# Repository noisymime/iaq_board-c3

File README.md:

# IAQ C3 (Indoor Air Quality) Board 
IAQ Board is a DIY (Do-It-Yourself) device for measuring internal air quality. This device is a fork of the [amazing work by Nikolay Kitanov](https://github.com/nkitanov/iaq_board) with the goals of updating the PCB to use the newer ESP32-C3 and to provide a more complete case and stand solution. 

**And here is my device. I am publishing all the details and documentation under '[open source hardware](https://en.wikipedia.org/wiki/Open-source_hardware)' CC-BY-CA license, so everyone can build, adapt and sell it, as long as share under the same license**

**Table of Contents**
   * [IAQ (Indoor Air Quality) Board](#iaq-indoor-air-quality-board)
      * [What exactly is this thing?](#what-exactly-is-this-thing)
      * [Who can build it?](#who-can-build-it)
      * [What about ordering a device?](#what-about-ordering-a-device)
   * [Components Details](#components-details)
      * [1. PCB](#1-pcb)
      * [2. Holder case](#2-holder-case)
      * [3. Microcontroller Board](#3-microcontroller-board)
      * [4. Dust Sensor](#4-dust-sensor)
      * [5. CO2 sensor](#5-co2-sensor)
      * [6. Temperature/Humidity/Pressure sensor](#6-temperaturehumiditypressure-sensor)
      * [7. Ambient Light Sensor](#7-ambient-light-sensor)
      * [8. LEDs](#8-leds)
      * [9. Displays](#9-displays)
      * [10. Volatile Organic Compound sensor](#10-volatile-organic-compound-sensor)
      * [11. Other electrical components](#11-other-electrical-components)
      * [Can you skip components?](#can-you-skip-components)
   * [Bill of Materials (BOM)](#bill-of-materials-bom)
   * [Firmware](#firmware)
   * [Schematic](#schematic)
   * [Soldering tips](#soldering-tips)
   * [User manual](#user-manual)
         * [Multi function button](#multi-function-button)
         * [LED Brightness control and correction](#led-brightness-control-and-correction)
   * [FAQ](#faq)
            * [<em>Can I power it from a battery?</em>](#can-i-power-it-from-a-battery)
            * [<em>Can it be installed outdoors?</em>](#can-it-be-installed-outdoors)
            * [<em>How to calibrate MH-Z19B CO2 sensor?</em>](#how-to-calibrate-mh-z19b-co2-sensor)
            * [<em>How to calibrate SGP30 VOC sensor?</em>](#how-to-calibrate-sgp30-voc-sensor)
            * [<em>How to connect to WiFi?</em>](#how-to-connect-to-wifi)
            * [<em>How to add it in Home Assistant?</em>](#how-to-add-it-in-home-assistant)
            * [<em>What if some of the sensors/displays is disconnected while the device works?</em>](#what-if-some-of-the-sensorsdisplays-is-disconnected-while-the-device-works)
         * [<em>What about short circuits of the exposed electronics?</em>](#what-about-short-circuits-of-the-exposed-electronics)
   * [More Tech Details](#more-tech-details)
   * [Known issues](#known-issues)
   * [License](#license)

## What exactly is this thing?
The device is based on widely available and cheap essential components ([MCU](https://en.wikipedia.org/wiki/Microcontroller) and sensors). The core component is a simple [PCB](https://en.wikipedia.org/wiki/Printed_circuit_board) (printed circuit board) that's why I called it **IAQ Board**. The board integrates all the components in a very small footprint (size of a cigarette box). All parts are soldered on it and everyone can assemble it with basic soldering skills. The total price if you build it yourself is about $75 AUD. For these amount of money you get the following air parameters measured adequately (you might not install all sensors if you want to save money): 
- [X] ***Temperature / Humidity / Pressure***
- [X] [***Air particles PM1, PM2.5, PM10***](https://en.wikipedia.org/wiki/Particulates)
- [X] [***Carbon Dioxide with NDIR sensor***](https://en.wikipedia.org/wiki/Indoor_air_quality#Carbon_dioxide)
- [X] [***Air Quality Index by EPA, based on 24h average PM2.5 particles***](https://airindex.eea.europa.eu/Map/AQI/Viewer/)
- [X] [***Ambient light***](https://en.wikipedia.org/wiki/Illuminance)
- [X] [***Total VOC (volatile organic compound)***](https://en.wikipedia.org/wiki/Volatile_organic_compound)
- [X] ***equivalent CO2 (not very correct compared with the NDIR sensor, but it's provided by the VOC sensor)***

**On top of that:**
- [X] ***One OLED display to show the data ***
- [X] ***three RGB wide angle LEDs with auto brightness. LED1 indicates PM2.5, LED2 - Air quality index, LED3 - CO2.*** 
- [X] ***auto night dimming of the displays and LEDs (can be disabled)***
- [X] ***MIN/MAX values of Temperature, PM2.5 and CO2, and 24h average PM2.5 value.***
- [X] ***multi function button for selection of the data to show on the display***
- [X] ***[firmware](https://en.wikipedia.org/wiki/Firmware) based on [ESPhome](https://esphome.io/), the device can be [directly added](https://esphome.io/components/api.html) in [Home Assistant](https://www.home-assistant.io/)***
- [X] ***WiFi access to the device with http server and [REST API](https://esphome.io/web-api/index.html) and [esphome native API](https://esphome.io/components/api.html)  to read the sensor data***

## Who can build it?
The device is just a simple PCB board and almost everyone with some soldering skills can assemble it in a few steps:
1. [Download the PCB files](kicad/) and print the PCB somewhere like https://jlcpcb.com/
2. Buy some components (listed in the bill of materials section) from Aliexpress or any other source.
3. Solder everything on the board. With the exception of the ambient light sensor, all the rest is pretty easy with general soldering skills. Soldering light sensor can be done with regular soldering iron, but because of the small size of the IC, it's easier if you have heat gun or SMD reflow oven/plate. [Here is video how to complete device from assembled PCB.](https://www.youtube.com/watch?v=b2oDBgN3h1w)
4. Flash the microcontroller with the esphome firmware [following the manual](firmware/). You can write your own firmware if you have the skills. :smile: 
5. Print the holder case on 3D printer if you wish. I have some sensors without it and they are perfectly fine, so it's up to you.

If you have experience with electronics and microcontrollers just check the [schematics](kicad/) and make whatever you wish - build your own firmware, do another PCB, connect external sensors, don't use it at all because you can make it better :smile:. The device is quite simple for embedded electronics enthusiasts anyway...

## What about ordering a device?
I made this device for me and then decided to share it. I think a lot of people might be interested to have such air quality sensor. I did not have intension to make money from it, that's why it's "open hardware" and I publish all of the information, so everyone can build it. 

However I know that someone might be interested in the device, but lack the skills to build it. [Please follow this link for more details.](ordering.md)

# Components Details

## 1. PCB

The PCB (printed circuit board) is very simple and compact. It's 70x43mm (photos above are showing it larger than the actual size). It just connects a few sensors, microcontroller and displays. I wanted to integrate it in as much smaller footprint as possible, so the whole device is like a cigarette box. Most of the parts are surface mounted which makes the soldering just a bit more complicated, but still not a big deal. And of course it could be integrated even more by soldering all individual components on the PCB but then it's not really a hobby project anymore and much more difficult to build it.
It's designed on [KiCad](https://kicad.org/) and in the [kicad folder](kicad/) you can find full KiCad project, PCB gerber files, etc.
## 2. Holder case

STL files for a case and stand are provided and can be printed on any standrd 3D printer.

## 3. Microcontroller Board
This is the primary difference between this board and the original by [nkitanov](https://github.com/nkitanov/iaq_board). I am using the newer ESP32-C3 Supermini which is not only faster and more compact, but has a USB-C connector on it rather than micro-USB

## 4. Dust Sensor

Dust sensor is the Chinese [Plantower PMS7003]([http://www.plantower.com/en/content/?110.html](https://www.plantower.com/en/products_33/76.html)) - 1, 2.5 and 10 micron particle laser sensor. It's very small and is perfect for indoor environment. 
## 5. CO2 sensor

Carbon dioxide sensor is the Chinese [Winsen MH-Z19B](https://www.winsen-sensor.com/sensors/co2-sensor/mh-z19b.html) - the most expensive part of the device. It's quite popular for hobby air quality meters and can [adequatly measure](https://www.circuits.dk/testing-mh-z19-ndir-co2-sensor-module/) up to 5000 ppm CO2 concentration.

**Keep in mind that there are some fake MH-Z19B sensors, [explained here](https://revspace.nl/MH-Z19B#Fake_MH-Z19B_.28black_PCB.29).**
## 6. Temperature/Humidity/Pressure sensor

This sensor is the popular [Bosch BME280](https://www.bosch-sensortec.com/products/environmental-sensors/humidity-sensors-bme280/), mounted on 3.3V only breakout board from China. There are also smaller [breakout boards](http://www.cncroutersource.com/breakout-boards.html) from China working both on 5V and 3.3V, but these have voltage regulator which can theoretically warm the board and change the temperature reading. That's why I use the boards with 3.3V only.

**Please note that due to semiconductor shortage these are difficult to find now (June 2021). I am currently using my own breakout where I solder the BME directly. BME280 as IC can be found occasionally in stock from DigiKey**
## 7. Ambient Light Sensor

The light sensor is [TSL 2561](https://ams.com/tsl2561) and it's the only sensor you need to solder directly on the board without a breakout board. I added this sensor not because I need to measure the ambient light but because I am a brightness freak, and I need the LEDs brightness to depend on the ambient light. Also wanted during the night when the lights are off the device to turn off the LEDs and displays automatically. You can also change the behavior of this brightness control and I spend some extra time developing the config only for the brightness features. :smile:
## 8. LEDs

The device has three [Neopixel 5050](https://www.digikey.com/catalog/en/partgroup/neopixel-rgb-5050-led-with-integrated-driver-chip-100-pack/70939) RGB multicolor LEDs. These LEDs are mostly found in the colorful LED strips and are controlled over a single wire. In my esphome based firmware left LED color is indicating the level of PM2.5 and change the colors depending on the value. Middle (LED2) indicates Air Quality Index based on PM2.5 only and the right one (LED3) indicates CO2 value. Keep in mind PM2.5 values are close to [EEA](https://www.eea.europa.eu/) levels (especially AQI). Some other devices like Xiaomi Air Purifiers have some very high levels on their displays and logic - it's green up to 70 microns which is already considered unhealthy both by EEA and EPA. In China "healthy" is considered bellow 50 microns. That's why AUTO mode of these Chinese devices [works so bad](https://smartairfilters.com/en/blog/xiaomi-auto-mode-leaves-air-unsafe-86-hours/). I try to keep indoor PM2.5 around 5-10 microns. I normally control my purifiers by Home Assistant and do not rely on their auto logic. If you have Xiaomi Purifier it can still show green, and the iaq device shows stable red, but it is correct according to the EU regulations.

**Colors of the LEDs depends on this table:**
PM2.5 value (um/m3)<br>LED 1 | [AQI by EEA (Air Quality Index for PM2.5 24h average)](https://airindex.eea.europa.eu/Map/AQI/Viewer/)<br>LED 2 | CO2 value (ppm)<br>LED 3 | Color |  R  |  G  |  B
:-----------------: | :-------------: | :-------------: | :---: | :-: | :-: | :-: 
< 10 | < 10 (Good) | < 700 |  | off | on | off 
11 - 20 | 10 - 20 (Fair) | 700 - 1000 |  | off | on | on 
20 - 30 | 20 - 25 (Moderate) | 1000 - 1500 |  | on | on | off 
30 - 40 | 25 - 50 (Poor) | 1500 - 2100 |  | on | off | on 
\> 50 | > 50 (Very Poor) | > 2100 |  | on | off | off 

## 9. Display
The display is the popular SSD1306 128x64 OLED display that is wideley and cheaply available on Aliexpress and eBay. 

## 10. Volatile Organic Compound sensor
This is the [Sensirion SGP30](https://www.sensirion.com/en/environmental-sensors/gas-sensors/sgp30/) senor mounted on a breakout board from China. I do not use it on all my devices, but I added it because I can. :smile: Also with it the device measures almost completely the internal air quality. SGP30 is also showing equivalent CO2 based on VOC but it's not precise compared with MH-Z19B NDIR sensor. Also it needs periodic calibration hardcoded in the firmware which makes it more tricky to use.

Please [check here](https://github.com/nkitanov/iaq_board/issues/10#issuecomment-798994427) for the known issues with these boards.

## 11. Other electrical components

The device has 2 buttons - one for selection screens and settings, and another micro button for calibration of the CO2 sensor to 400ppm if you keep it pressed for more than 7 sec. 

There are also four [surface mounted](https://en.wikipedia.org/wiki/Surface-mount_technology) [bypass capacitors](https://en.wikipedia.org/wiki/Decoupling_capacitor) for the ambient light sensor and the LEDs.

## Can you skip components?
Yes. The minimum you need is the [microcontroller board](#3.-microcontroller-board). However since you don't have any sensors, you won't get any data. :smile: You can add only the sensors needed. Also if you skip ambient light sensor there will be no auto brightness control and the LEDs will operate always at 25% intensity. Installing only the ambient light sensor without any of the displays or any of the other [I2C](https://en.wikipedia.org/wiki/I%C2%B2C) sensors (BME280, SGP30) will not work as there are no [pullup resistors](https://en.wikipedia.org/wiki/Pull-up_resistor) on the PCB for the I2C bus since it uses the resistors of the external breakout boards.

# Bill of Materials (BOM)
Bellow is the list of all parts needed to assemble the device with links to sources where you can get them. Of course other sources can be used, just pay attention that the items are identical with the listed bellow. For example the SSD1306 display can be found with similar physical look and dimensions, but pins are not the same.

Schematic Ref | ITEM | pcs | Comment
--------------| ---- | :-: | -------
| | PCB Board | 1 | in [kicad folder](kicad) you can find all the data and GERBER PCB design files
U1 | [ESP32-C3 Supermini](https://vi.aliexpress.com/item/1005007577443695.html) | 1
U2 | [PMS7003 Sensor](https://www.aliexpress.com/item/32832444694.html?spm=a2g0s.9042311.0.0.27424c4dKxsO6Z) | 1 | don't use the 2x5pin 1.27mm receptacle which comes normally wit these sensors, explanation is bellow
U3 | [SSD1306 Display](https://www.aliexpress.com/item/32956051129.html?spm=a2g0o.productlist.0.0.523365fcQkP3XC&algo_pvid=b62bd3ab-fe19-479e-bc50-b2c68dd35525&algo_expid=b62bd3ab-fe19-479e-bc50-b2c68dd35525-25&btsid=67d67e08-4ad1-4c08-8cec-e378bae47fc6&ws_ab_test=searchweb0_0,searchweb201602_9,searchweb201603_55) | 1 | pay attention to correct pin order if you are buying from another source, as there are similar 4pin boards with different pinout
U4 | [BME280 breakout board](https://www.aliexpress.com/item/4000166540445.html?spm=a2g0o.productlist.0.0.363a562ely2LZq&algo_pvid=b0bd6068-edbb-4f9c-aa24-92324f726eda&algo_expid=b0bd6068-edbb-4f9c-aa24-92324f726eda-8&btsid=3927b67d-2f89-4594-9f47-b017e00ef8a0&ws_ab_test=searchweb0_0,searchweb201602_9,searchweb201603_55) | 1 | only 3.3V version with 6 pins which have both I2C and SPI. **Please note that due to semiconductor shortage these are difficult to find now (June 2021). I am currently using my own breakout where I solder the BME directly. BME280 as IC can be found occasionally in stock from DigiKey**
U5 | [MH-Z19B Sensor](https://www.aliexpress.com/item/1005001865093513.html?spm=2114.12010610.8148356.5.5b7387a5ZmuUlX) | 1 | **Beware for fake sensors, as [explained here](https://revspace.nl/MH-Z19B#Fake_MH-Z19B_.28black_PCB.29). Buy from Winsen official store in Aliexpress.**  
U6 | [SGP30 breakout board](https://www.aliexpress.com/item/4000004614708.html?spm=a2g0o.productlist.0.0.688164abtt6ZRA&algo_pvid=7f813f70-3c1d-42ee-b6cf-9bf501c47314&algo_expid=7f813f70-3c1d-42ee-b6cf-9bf501c47314-1&btsid=3f683b7d-631a-4373-b0a1-f574cd317549&ws_ab_test=searchweb0_0,searchweb201602_9,searchweb201603_55) | 1
U7 | [TLS2561 light sensor](https://www.aliexpress.com/item/33056165996.html?spm=a2g0s.9042311.0.0.15314c4draqb6x) | 1
C1-C4 | [0.1 uF SMD Capacitor](https://bg.farnell.com/wurth-elektronik/885012207016/cap-0-1-f-10v-10-x7r-0805/dp/2534051?st=smd%20capacitors) | 4
D1-D3 | [Neopixel 5050 LED](https://www.aliexpress.com/item/4000750610574.html?spm=a2g0o.productlist.0.0.55a96722mpqDCp&algo_pvid=4be2d94a-875a-4e56-af12-1f6a3dcdf49f&algo_expid=4be2d94a-875a-4e56-af12-1f6a3dcdf49f-5&btsid=0bb0623416009856118282154ebe61&ws_ab_test=searchweb0_0,searchweb201602_,searchweb201603_) | 3
| SW1 | [Tactile Switch TL3305](https://www.digikey.com.au/en/products/detail/e-switch/TL3305BF160QG/5816182) | 1
| SW2 | [Tactile Switch TL3342](https://www.digikey.com.au/en/products/detail/e-switch/TL3342F450QG/4029404) | 1
| | [PCB Receptacle, 1.27 mm, 10 Contacts](https://bg.farnell.com/amphenol-icc-fci/20021311-00010t4lf/receptacle-vert-1-27mm-tht-10way/dp/1865313) | 1 | This PCB Receptacle is for connecting PMS7003 dust sensor. Keep in mind these sensors come with such connector included but it's slightly taller and makes a gap of about half mm between sensor and PCB which is not ok.
| | [SMD PCB Receptacle 8 pins](https://uk.farnell.com/samtec/ssm-108-l-sv/receptacle-2-54mm-vert-8way/dp/1668259?st=ssm-108-l-sv%20pcb%20receptacle) | 3 | two are needed for the MCU board, 3rd you can skip. It's for extra pins on the PCB but with ESP32 MCU not needed so much as extra headers can be soldered directly on it's board
| | [PCB Receptacle 4 pin](https://uk.farnell.com/samtec/bcs-104-l-s-te/receptacle-2-54mm-vert-4way/dp/1667470?ost=bcs-104-l-s-te) | 4 | four is needed if all sensors are installed
| | [Holder case](case_model) | 1 | it's not required to have it but it makes the device completed
| | [Display holder](case_model) | 1 | This small 3D printed part is holding tight the display from flapping 
| | [Various 2.54 headers](https://www.ebay.co.uk/itm/10pcs-40-pin-2-54mm-Breakaway-Male-Header-for-PCB-Breadboard-1x40-Single-Row-UK/262755464818?epid=20008873513&hash=item3d2d723672:g:st8AAOSwMsZdNw5x) | | You will need these for the CO2 sensor if you don't have available. Normally they come together with the breakout boards.

# Firmware
Firmware is created with [ESPHome](https://esphome.io/index.html). The binary file, configuration and instructions are located in [firmware folder](firmware/).

# Schematic
Find all KiCad project in [kicad folder](kicad/) with schematic, PCB design file, 3D models, etc. In schematic U1 (microcontroller board) is based on ESP8266 version (original Wemos D1 mini).

# User manual
It's quite simple, the device have only one "multi functional" button SW1, and one micro button SW2 for calibration of the CO2 sensor.

### Multi function button
- Short press "rotates" the data displayed on the right bigger display. By default it starts showing only PM2.5 and CO2 with larger fonts as these are the most important air quality parameters. This is also the default "screen" and every time the device is restarted it will show that screen. The display is quite small (128x64 pixels) so some of the text is shortened like P1 (for PM1), C (for CO2), etc. Each short press of the button rotates this sequence:
```
DEFAULT==================================================================MIN/MAX===============
PM2.5      AQI        Temperature    PM1         Amb.Light  PM1         Temp. MIN        Displays OFF
CO2 ----> Index ----> Humidity ----> PM2.5 ----> TVOC ----> PM2.5 ----> PM2.5 MIN ----> (both displays  
 ^      PM2.5 24h     Pressure       PM10        eCO2       PM10        CO2 MIN          turned off)
 |                                                          Temperature Temp. MAX             |
 |                                                          Humidity    PM2.5 MAX             |
 |                                                          Pressure    CO2 MAX               |
 | _ _ _ _ _ _ _ _ _ _ _ _ _ _ _ _ _ _ _ _ short click_  _ _ _ _ _ _ _ _ _ _ _ _ _ _ _ _ _ _ _|
```

- Press and hold the button from **2 to 5 sec**: On the display you see `LEDs status: OFF`. This means the status LEDs will be tuned off. Do the same to toggle back to `LEDs status: ON`. This setting is saved in the non volatile memory, so it will keep it's setting even if the MCU is restarted. 
- Press and hold the button from **5 to 10 sec**: On the display you see `Night dim: OFF`. This means the LEDs and displays will not be turned off if ambient light fall under 2 lux. Do the same to toggle back to `Night dim: ON`. This setting is saved in the non volatile memory, so it will keep it's setting even if the MCU is restarted. 
- Press and hold from **10 to 15 sec**: On the display you see `MIN-MAX Reset!`. It reset the minimum and maximum values of temperature, PM2.5 and CO2 on screen 6. Please note these resets each time the device is restarted. Keep in mind that 1.5 min after boot and reset, values of CO2 and temperature might not be correct.
- Press and hold from **15 to 20 sec**: It will increase LED brightness correction with +5%. When it reaches +40% another press and hold will make it 0% again. 
- Press and hold from **20 to 30 sec**: On the display for 20 sec it will show the following diagnostic data:
```
YAML ver: (shows version of the esphome yaml config)
ESPHome ver: (ESPHome version which build the firmware)
IP: (IP address if connected to WiFi)
Connected to: (SSID of the wifi, if connected)
LED brightness: (brigtness correction of the LEDs)
```
### LED Brightness control and correction
Led brightness is controlled periodically (each 3 sec), proportional of the ambient light measured by the TLS2561 sensor. If there is no ambient light sensor installed LEDs are constant at 25%, but auto turn off will also not work. Logic of this simple auto control is configured in [this code](firmware/includes/brightness.yaml).

Also by default setting of these LEDs are to begin from 11% brightness. If it's bellow 11% they are turned off. As mentioned in the LED description setting these Chinese LEDs comes with different intensity and the ones listed in Bill of Materials section are too weak at the lowest setting. That's why I added brightness correction setting which can go from 0% to +40% in 5% step. This be done with press and hold the multi function button from 15 to 20 sec (explained above). This setting is saved in the non volatile memory of the MCU and it does not have to be configured after each reset. Alternatively if the device is added in Home Assistant, you will see a template switch called `brightness_correction`, which is doing exactly the same thing as the button on pin.

# FAQ
#### *Can I power it from a battery?*

The device is powered from regular micro USB cable with 5V and consumes between 100-250 mA. You can power it with USB battery pack but not for too long (for example 4000 mAh battery will be depleted in about 20h). If you need to operate it from a battery, firmware have to enter the MCU in a [deep sleep](https://esphome.io/components/deep_sleep.html) mode periodically. You have to build your own firmware. I do not run any of my devices in deep sleep as I do not see a reason for that.
#### *Can it be installed outdoors?*

The device is not waterproof. It can run outdoors if you install it in enclosure which is protecting it from water. It can handle high humidity maybe (never tested it). However the main purpose of the device is to be an internal air quality monitor. Measuring CO2 and VOC outside does not makes too much sense, but it can be used for dust pollution monitoring.

#### *How to calibrate MH-Z19B CO2 sensor?*

Periodically (let's say one time per month) and after installation of a new sensor calibration needs to be performed. The calibration is done by exposing it to the outside air which have about 400ppm CO2 concentration for about 20-30 min and then press and hold the micro button SW2 for more then 7 sec. In that way the value of the sensor is "zeroed" at 400 ppm. Alternatively if the device is added in Home Assistant, there is a template switch called `switch.co2_sensor_zero_calibration` and you just turn it on. It's doing the same as pusing the button but you are doing it remotely over the WiFi. [Here](https://www.circuits.dk/testing-mh-z19-ndir-co2-sensor-module/) are more details about this sensor and calibration.

#### *How to calibrate SGP30 VOC sensor?*

It's explained in [ESPHome manual](https://esphome.io/components/sensor/sgp30.html). You need periodically to update the firmware which is quite easy if you use Home Assistant. In my initial tests I noticed even without calibration value, the sensor shows some values and can detect smells, alcohol vapors, etc. 

#### *How to connect to WiFi?*

After 1 minute of unsuccessful WiFi connection attempts, the microcontroller will start a WiFi hotspot with name `iaq_device` and password `12345678`. When you connect to this fallback hotspot, the web interface should open automatically (see also login to network notifications). If that does not work, you can also navigate to http://192.168.4.1/ manually in your browser. Then type name and password of your local wifi hotspot, click save and MCU will restart and try to connect to the provided network. Additionally from this captive portal you can upload a new firmware.

#### *How to add it in Home Assistant?*

If you have Home Assistant you have to [install the ESPHome addon](https://esphome.io/guides/getting_started_hassio.html), and after that [add the device](https://esphome.io/components/api.html). All sensors, switches, LEDs will appear automatically as entities in Home Assistant. Then you can add them on the dashboard, here is one of my devices added on Home Assistant dashboard with all data from it.

#### *What if some of the sensors/displays is disconnected while the device works?*

Some of the sensors can be accidentally disconnected as on the original design they are not soldered on the PCB but are connected on a header receptacle. No worries with that. On the display you will see `NaN` and it means there is no value from the sensor or it's out of boundaries. Just reseat the sensor and push the reset button on the MCU board or  disconnect and reconnect the USB cable.

### *What about short circuits of the exposed electronics?*

Since all the components are exposed, there is some risk of making a short circuit with a metal object. The power supply is just 5V with limited current so it shouldn't be a big worry. However be careful not to short circuit anything with a conductive object as theoretically this can damage a component. 

# Known issues
These are valid for ESP32 MCU:
- Poor quality of the SGP30 VOC sensor breakout boards from China. The issues and fixes [explained here](https://github.com/nkitanov/iaq_board/issues/10#issuecomment-798994427).
- When you open [the web interface](https://esphome.io/components/web_server.html) of the device - it resets sometimes.
- I had a batch of Neopixel 5050 LEDs which are a bit brighter than the one linked in the BOM section and sometimes they switch to white color and 100% intensity. This is fixed in max 3 sec when correct color and brightness is set back again. These LEDs are set sequentially by their protocol so apparently it interprets wrongly set command or something. This is not happening with the LEDs linked in BOM but keep it in mind that it can happen with some LEDs (especially if they are from a bright batch).
- In the configuration I run the temperature with -1 degreeC offset. I found out these sensors shows a bit higher, and also there is some minimal temperature rise from conducted heat from the PCB. Always connect the BME280 sensor high above the PCB as in my design with the 4 pin receptacle. If you solder it lower on the PCB it might run hotter. For even more precise temperature measurement you can calibrate in esphome the value very precisely if you have access to calibrated thermometer. I was thinking also to experiment with thermocouple on the hole of the dust sensor fan so it can not pick up extra heat. This is in case if you need to use this temperature as input for a thermostat, as I do. 

These are valid for ESP8266 MCU (including the previous issues), not recommended to use that MCU because of the bellow issues:
- periodic [WDT resets](https://en.wikipedia.org/wiki/Watchdog_timer) depending of the WiFi activity, if MCU not connected to WiFi, it's ok. This is caused by the bit banging of the UART interface.
- web server is almost unusable as it needs a lot of memory which is not available on this tiny MCU
- unstable [AP fallback mode](https://esphome.io/components/wifi.html#access-point-mode), causing WDT resets, so sometimes not easy to connect to WiFi without hardcoding the credentials in the firmware

# License 
The device is [Open-source hardware](https://en.wikipedia.org/wiki/Open-source_hardware), [licensed by Open Source Hardware Association](https://certification.oshwa.org/bg000078.html). 

- Hardware is licensed under [CERN-OHL-W v2](https://ohwr.org/cern_ohl_w_v2.txt).
- Software is licensed under [Apache License 2](https://www.apache.org/licenses/LICENSE-2.0)
- Documentation is licensed under [CC-BY-SA-4.0](https://creativecommons.org/licenses/by-sa/4.0/).

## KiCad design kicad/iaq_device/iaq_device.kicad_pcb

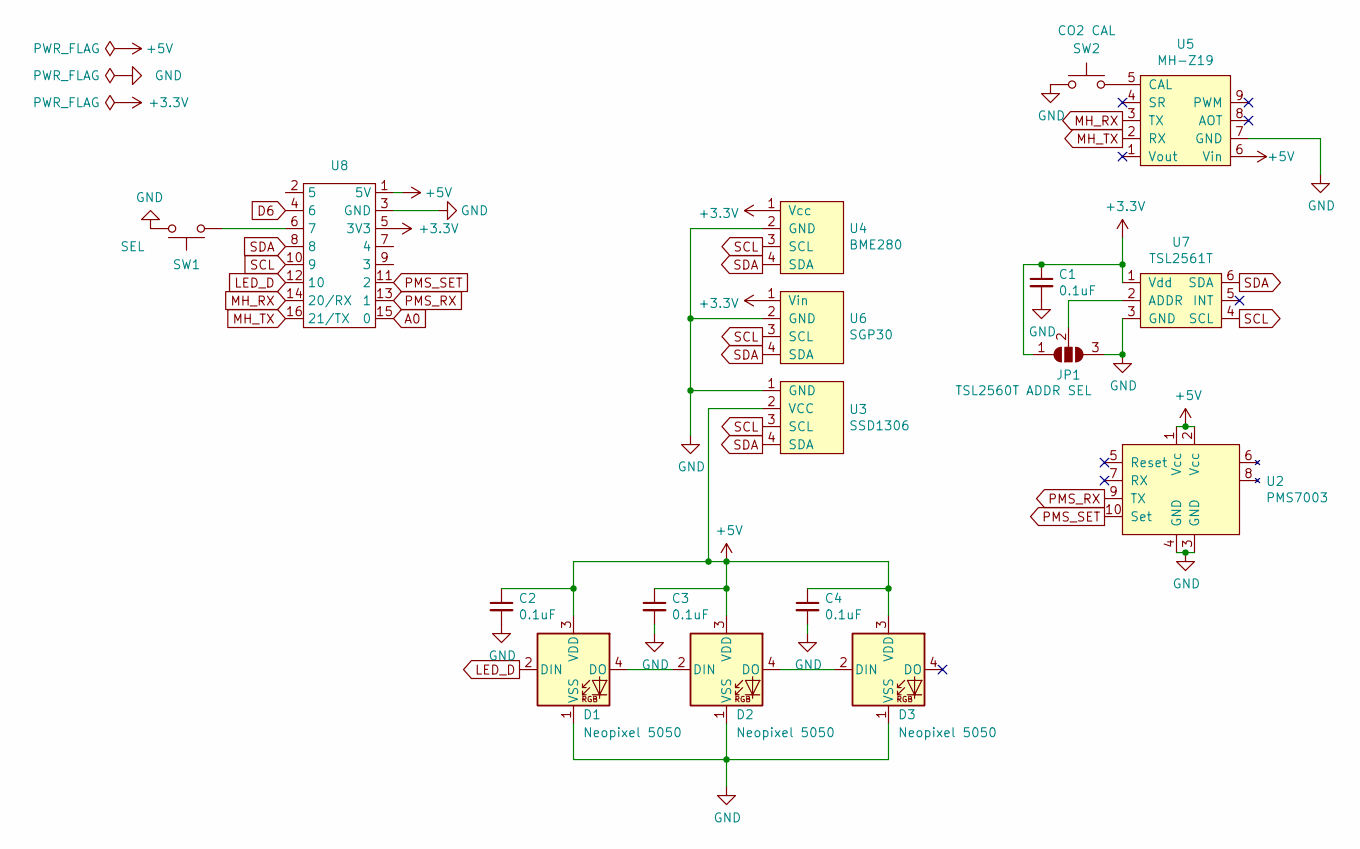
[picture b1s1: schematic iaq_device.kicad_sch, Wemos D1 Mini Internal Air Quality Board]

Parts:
C1, C2, C3, C4: 0.1uF; C_0805_2012Metric
D1, D2, D3: Neopixel 5050; LED_Inolux_IN-PI554FCH_PLCC4_5.0x5.0mm_P3.2mm
JP1: TSL2560T ADDR SEL; SolderJumper-3_P1.3mm_Open_RoundedPad1.0x1.5mm
SW1: SEL; SW_SPST_TL3305B
SW2: CO2 CAL; SW_SPST_TL3342
U2: PMS7003
U3: SSD1306; SSD1306_I2C_0.96in
U4: BME280; BME280_breakout_6pin
U5: MH-Z19
U6: SGP30; SGP30_breakout_4pin
U7: TSL2561T
U8: ESP32-C3 SUPERMINI

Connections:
+3V3: C1.1, JP1.1 (A), U4.1 (Vcc), U6.1 (Vin), U7.1 (Vdd), U8.5 (3V3)
+5V: C2.1, C3.1, C4.1, D1.3 (VDD), D2.3 (VDD), D3.3 (VDD), U2.1 (Vcc), U2.2 (Vcc), U3.2 (VCC), U5.6 (Vin), U8.1 (5V)
A0: U8.15 (0)
D6: U8.4 (6)
GND: C1.2, C2.2, C3.2, C4.2, D1.1 (VSS), D2.1 (VSS), D3.1 (VSS), JP1.3 (B), SW1.2, SW2.1, U2.3 (GND), U2.4 (GND), U3.1 (GND), U4.2 (GND), U5.7 (GND), U6.2 (GND), U7.3 (GND), U8.3 (GND)
LED_D: D1.2 (DIN), U8.12 (10)
MH_RX: U5.3 (TX), U8.14 (20/RX)
MH_TX: U5.2 (RX), U8.16 (21/TX)
unnamed: D1.4 (DO), D2.2 (DIN)
unnamed: D2.4 (DO), D3.2 (DIN)
unnamed: JP1.2 (C), U7.2 (ADDR)
unnamed: SW2.2, U5.5 (CAL)
unnamed: SW1.1, U8.6 (7)
PMS_RX: U2.9 (TX), U8.13 (1)
PMS_SET: U2.10 (Set), U8.11 (2)
SCL: U3.3 (SCL), U4.3 (SCL), U6.3 (SCL), U7.4 (SCL), U8.10 (9)
SDA: U3.4 (SDA), U4.4 (SDA), U6.4 (SDA), U7.6 (SDA), U8.8

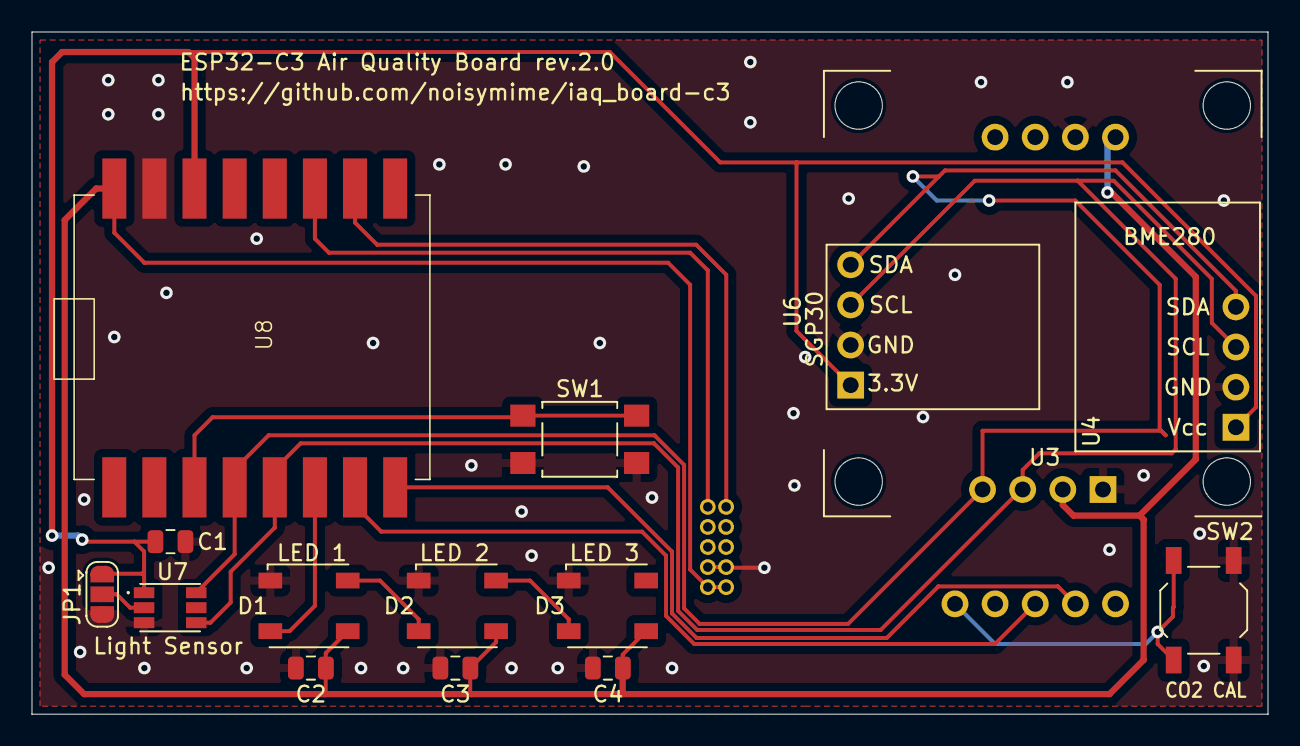
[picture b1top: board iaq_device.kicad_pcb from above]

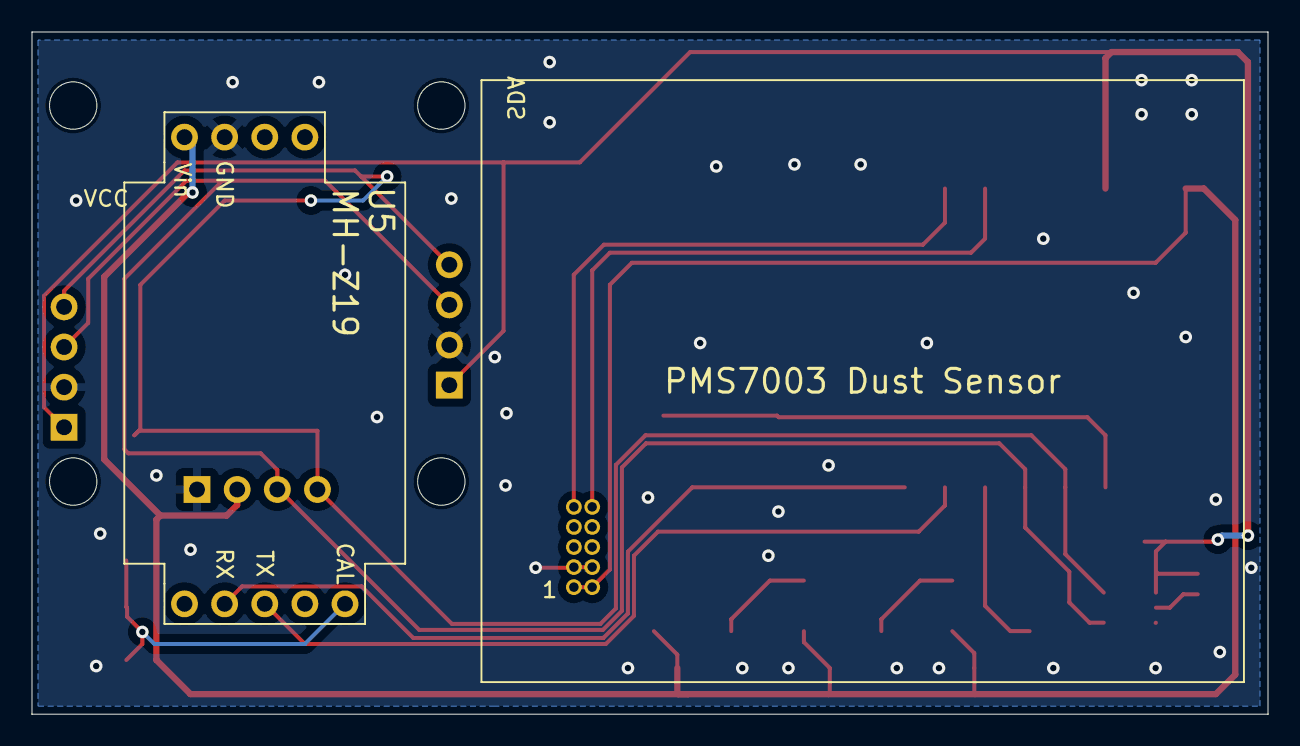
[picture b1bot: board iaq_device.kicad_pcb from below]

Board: 2 copper layers, 78.2 x 43.2 mm, 17 parts (2 on the bottom side), 15 nets.

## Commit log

2024-03-15 Update iaq_board.yaml
    Update _i2c format for bme280
2024-06-16 Update iaq_board.yaml
    probably not required as update by now
2024-10-17 Initial commit of c3 board
2024-10-30 v2.0 of the C3 PCB files
2025-01-05 Updated design files
2025-01-05 Updated README and docs
2025-01-05 Further README updates

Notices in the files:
README.md:
License:
The device is [Open-source hardware](https://en.wikipedia.org/wiki/Open-source_hardware), [licensed by Open Source Hardware Association](https://certification.oshwa.org/bg000078.html).
- Hardware is licensed under [CERN-OHL-W v2](https://ohwr.org/cern_ohl_w_v2.txt).
- Software is licensed under [Apache License 2](https://www.apache.org/licenses/LICENSE-2.0)
- Documentation is licensed under [CC-BY-SA-4.0](https://creativecommons.org/licenses/by-sa/4.0/).
